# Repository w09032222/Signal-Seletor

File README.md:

# Signal-Seletor

It is a 2hp 3-channel DC-coupled CV controlled signal-seletor, input any signal between +-10V and you can output any one of the three inputs.there's an attenuator at the output for manually controlling the amplitude of the output signal.

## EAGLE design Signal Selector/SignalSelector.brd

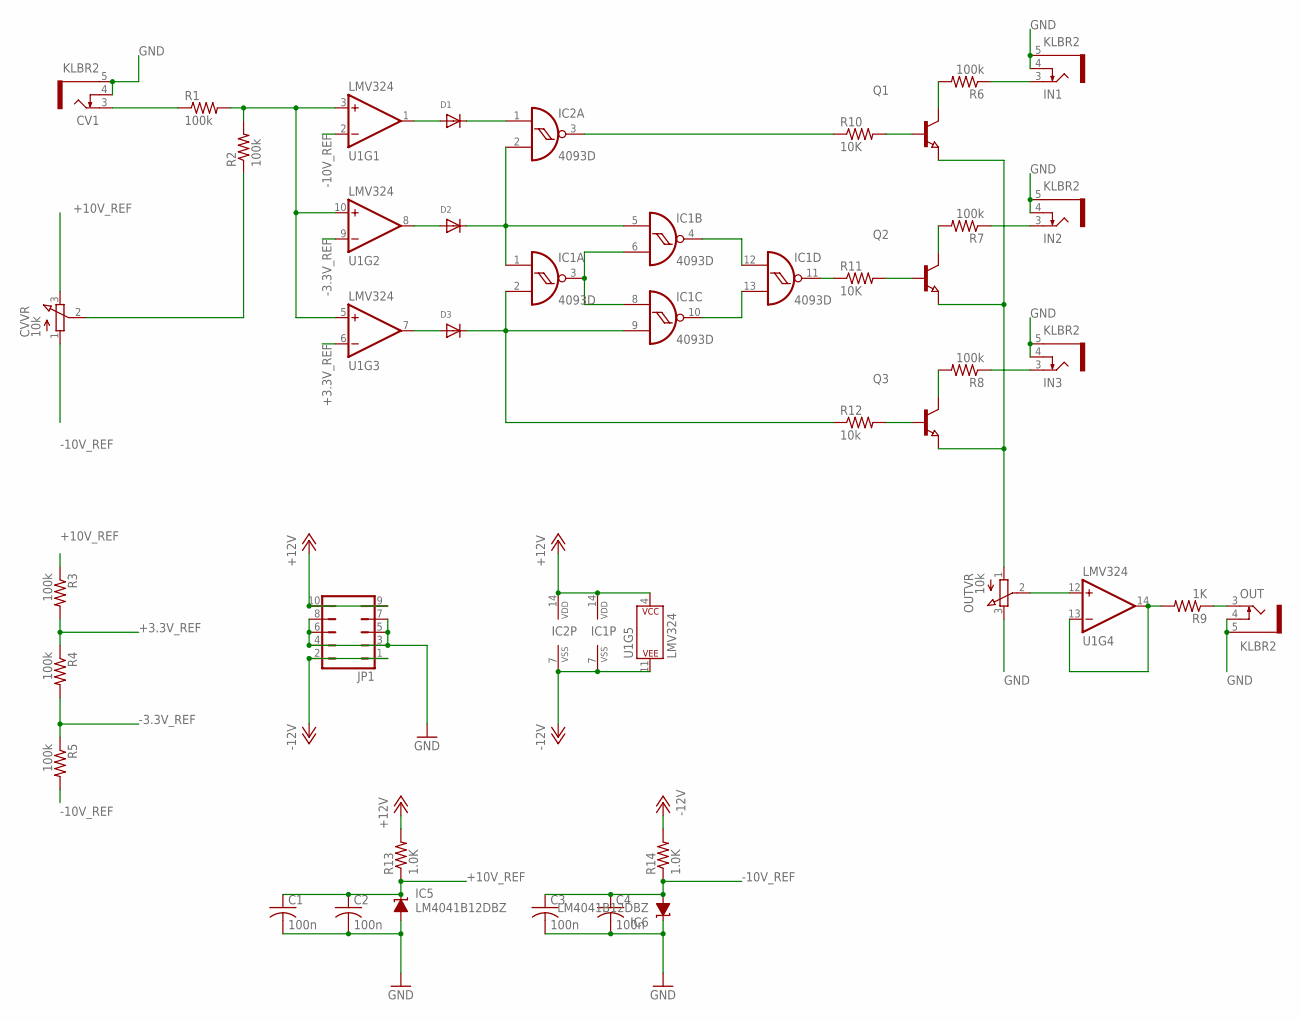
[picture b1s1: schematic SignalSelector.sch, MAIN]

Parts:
C1, C2, C3, C4: 100n; C0603
CV1: KLBR2
CVVR: 10k; 3RP/1610N
D1, D2, D3: DIODE_SOD-123FL; SOD-123FL
IC1, IC2: 4093D; SO14
IC5, IC6: LM4041B12DBZ; DBZ_R-PDSO-G3
IN1, IN2, IN3: KLBR2
JP1: JP5Q
OUT: KLBR2
OUTVR: 10k; 3RP/1610N
Q1, Q2, Q3: NPN-TRANSISTOR_SOT23; SOT23
R1, R2, R3, R4, R5, R6, R7, R8: 100k; R0603
R9: 1K; R0603
R10, R11: 10K; R0603
R12: 10k; R0603
R13, R14: 1.0K; R0603
U1: LMV324; SO14

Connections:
+3.3V_REF: R3.2, R4.1, U1.6 (-IN)
+10V_REF: C1.1, C2.1, CVVR.3 (E), IC5.1 (C), R3.1, R13.1
+12V: IC1.14 (VDD), IC2.14 (VDD), JP1.9, JP1.10, R13.2, U1.4 (P$V+)
-3.3V_REF: R4.2, R5.1, U1.9 (-IN)
-10V_REF: C3.1, C4.1, CVVR.1 (A), IC6.2 (A), R5.2, R14.1, U1.2 (-IN)
-12V: IC1.7 (VSS), IC2.7 (VSS), JP1.1, JP1.2, R14.2, U1.11 (P$V-)
GND: C1.2, C2.2, C3.2, C4.2, CV1.4, CV1.5, IC5.2 (A), IC6.1 (C), IN1.4, IN1.5, IN2.4, IN2.5, IN3.4, IN3.5, JP1.3, JP1.4, JP1.5, JP1.6, JP1.7, JP1.8, OUT.4, OUT.5, OUTVR.3 (E)
unnamed: CV1.3, R1.1
unnamed: R1.2, R2.2, U1.3 (+IN), U1.5 (+IN), U1.10 (+IN)
unnamed: D1.A, U1.1 (OUT)
unnamed: CVVR.2 (S), R2.1
unnamed: D2.A, U1.8 (OUT)
unnamed: D3.A, U1.7 (OUT)
unnamed: D1.C, IC2.1 (I0)
unnamed: D2.C, IC1.1 (I0), IC1.5 (I0), IC2.2 (I1)
unnamed: D3.C, IC1.2 (I1), IC1.9 (I1), R12.1
unnamed: IC1.3 (O), IC1.6 (I1), IC1.8 (I0)
unnamed: IC1.4 (O), IC1.12 (I0)
unnamed: IC1.10 (O), IC1.13 (I1)
unnamed: IC2.3 (O), R10.1
unnamed: Q1.1 (B), R10.2
unnamed: IC1.11 (O), R11.1
unnamed: Q2.1 (B), R11.2
unnamed: Q3.1 (B), R12.2
unnamed: OUTVR.1 (A), Q1.2 (E), Q2.2 (E), Q3.2 (E)
unnamed: OUTVR.2 (S), U1.12 (+IN)
unnamed: R9.2, U1.13 (-IN), U1.14 (OUT)
unnamed: Q1.3 (C), R6.2
unnamed: IN1.3, R6.1
unnamed: IN2.3, R7.1
unnamed: Q2.3 (C), R7.2
unnamed: Q3.3 (C), R8.2
unnamed: IN3.3, R8.1
unnamed: OUT.3, R9.1

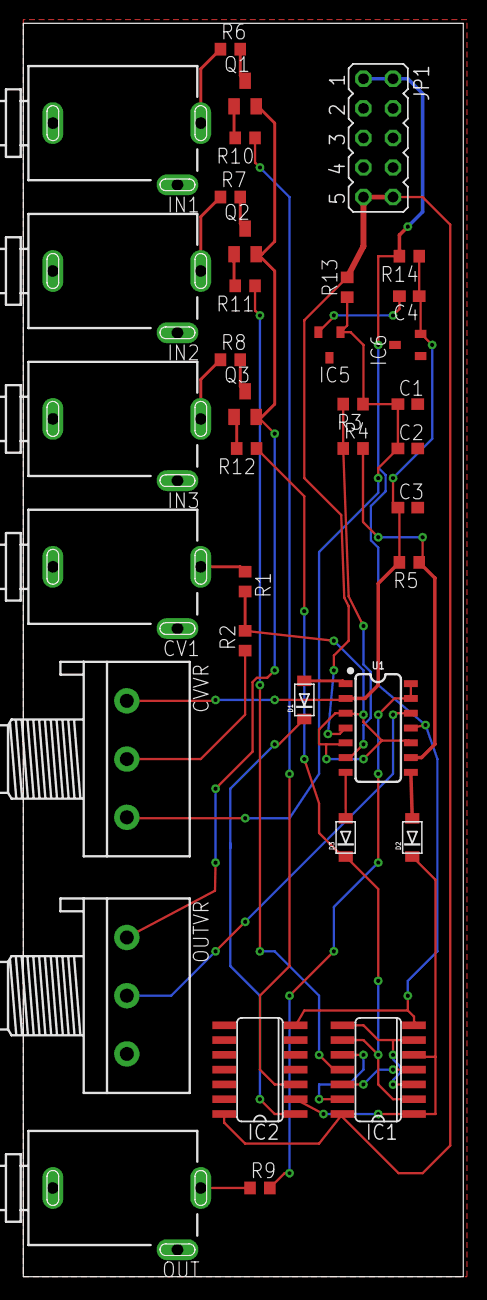
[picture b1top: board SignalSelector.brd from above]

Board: 2 copper layers, 37.8 x 107.6 mm, 37 parts (0 on the bottom side), 34 nets.

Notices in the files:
parts and their libraries:
SparkFun-IC-Amplifiers: Licensing: Creative Commons ShareAlike 4.0 International - https://creativecommons.org/licenses/by-sa/4.0
